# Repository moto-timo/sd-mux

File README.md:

# sd-mux

sd-mux stands for Secure Digital Multiplexer.

This is SD card switcher (multiplexer) designed to help automatic testing.

This project is sd-mux controller - binary for controlling sd-mux device.

Requirements:
  1. libftdi1 1.4 - development library
  2. popt - development library
  3. cmake - binary tool

Build:
 - enter into project directory
 - create 'build' directory
 - enter into "build" directory
 - run 'cmake ..'
 - run 'make'

Install:
 - enter into 'build' directory
 - run 'sudo make install' to install binary into '/usr/local/bin' (the default one) directory

Note:
If you want to install files into different directory then add argument to cmake command:
 cmake -DCMAKE_INSTALL_PREFIX=/usr ..
Then again run:
 make
 make install

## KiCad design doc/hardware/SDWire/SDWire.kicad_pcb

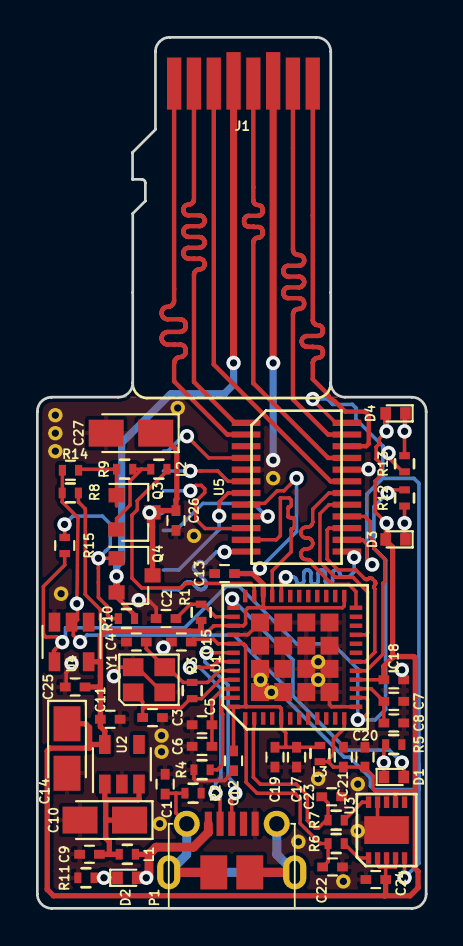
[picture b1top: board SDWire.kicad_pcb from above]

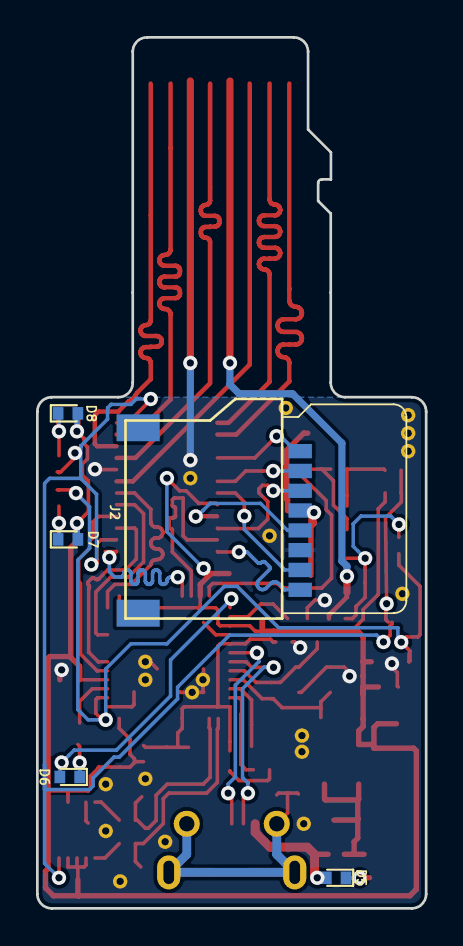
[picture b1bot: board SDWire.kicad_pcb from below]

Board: 2 copper layers, 21.6 x 48.4 mm, 63 parts (5 on the bottom side), 49 nets.

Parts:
C1, C2, C6, C8, C9, C11, C12, C13, C15, C17, C18, C20, C24, C25, C26: 100nF/16V; C_0402
C3, C4: 33p/50V; C_0402
C5, C7, C19, C21: 1uF/16V; C_0402
C10, C14, C27: 10uF/10V; CP_Tantalum_Case-A_EIA-3216-18_Reflow
C22, C23: 47pF; C_0402
D1, D6: OSB50402C1E; LED_0402
D2, D5: RED; LED_0402
D3, D7: BLUE; LED_0402
D4, D8: GREEN; LED_0402
J1: usd-plug; usd
J2: uSD Socket; usd-attend
L1, L2, L3: BLM15PD121SN1D; R_0402
P1: USB_OTG_MICRO_USB; micro_sub_molex
Q3, Q4: MMBT4403LT1; SOT-23
R1, R2, R9, R10: 10K; R_0402
R3: 1M; R_0402
R4: 12k 1%; R_0402
R5: 330R; R_0402
R6, R7: 27R; R_0402
R8: DNP; R_0402
R11, R12, R13, R14, R15: 1K; R_0402
U1: USB2640-HZH-02; QFN-48-1EP_7x7mm_Pitch0.5mm
U2: SPX3819M5; SOT-23-5
U3: FT200XD; DFN-10-1EP_3x3mm_Pitch0.5mm
U4: MC74HC1G04DTT1G; SOT-23-5
U5: TS3A27518EPWR; TSSOP-24
Y1: 24MHz; Crystal_SMD_2520-4pin_2.5x2.0mm

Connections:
+3V3: C11.1, C13.1, C14.1, C18.1, C20.1, C21.1, C24.1, C25.1, D3.2, D4.2, D7.2, D8.2, L3.1, R1.1, R8.2, U1.12, U1.16, U1.25, U1.34, U1.39, U2.5, U3.2, U3.3, U3.4, U3.7, U4.5, U5.8
/CLK_DUT: J1.5, U5.21
/CLK_TS: U1.21, U5.17
/CMD_DUT: J1.3, U5.19
/CMD_TS: U1.24, U5.18
/DAT0_DUT: J1.7, U5.23
/DAT0_TS: U1.18, U5.15
/DAT1_DUT: J1.8, U5.22
/DAT1_TS: U1.17, U5.16
/DAT2_DUT: J1.1, U5.2
/DAT2_TS: U1.33, U5.11
/DAT3_DUT: J1.2, U5.1
/DAT3_TS: U1.32, U5.13
/SOCKET_SEL: R8.1, R13.2, R14.2, U3.5, U4.2, U5.14, U5.24
/USB_B+: C23.1, R7.2, U1.2
/USB_B-: C22.1, R6.2, U1.1
/USB_UP+: P1.3, U1.42
/USB_UP-: P1.2, U1.43
/USD_VDD: C26.1, C27.1, J2.4, Q3.3, Q4.3
/VDD: D2.2, D5.2, L1.2, P1.1
/VDD_DUT: J1.4, Q4.2, R10.2
/VDD_TS: L2.1, Q3.2, R9.2
/~CD_TS: R12.2, R15.2, U1.14, U4.4
/~RESET: C2.1, R1.2, U1.38
GND: C1.2, C2.2, C3.2, C4.2, C5.2, C6.2, C7.2, C8.2, C9.2, C10.2, C11.2, C12.2, C13.2, C14.2, C15.2, C17.2, C18.2, C19.2, C20.2, C21.2, C22.2, C23.2, C24.2, C25.2, C26.2, C27.2, J1.6, J2.6, P1.5, R2.2, R4.2, R5.2, R11.2, U1.13, U1.40, U1.49, U2.2, U3.9, U3.11, U4.3, U5.5, U5.20, Y1.2, Y1.4
unnamed: C1.1, P1.6, R2.1
unnamed: C3.1, R3.2, U1.45, Y1.1
unnamed: C4.1, R3.1, U1.44, Y1.3
unnamed: C5.1, C6.1, U1.46
unnamed: C7.1, C8.1, U1.15
unnamed: C9.1, C10.1, L1.1, U2.1, U2.3
unnamed: C12.1, C15.1, C17.1, C19.1, L3.2, U1.5, U1.41, U1.48
unnamed: D1.1, D6.1, R5.1
unnamed: D1.2, D6.2, U1.37
unnamed: D2.1, D5.1, R11.1
unnamed: D3.1, D7.1, R12.1
unnamed: D4.1, D8.1, R13.1
unnamed: J2.1, U5.4
unnamed: J2.2, U5.6
unnamed: J2.3, U5.10
unnamed: J2.5, U5.9
unnamed: J2.7, U5.7
unnamed: J2.8, U5.12
unnamed: L2.2, U1.35
unnamed: Q3.1, R9.1, R14.1
unnamed: Q4.1, R10.1, R15.1
unnamed: R4.1, U1.47
unnamed: R6.1, U3.1
unnamed: R7.1, U3.10

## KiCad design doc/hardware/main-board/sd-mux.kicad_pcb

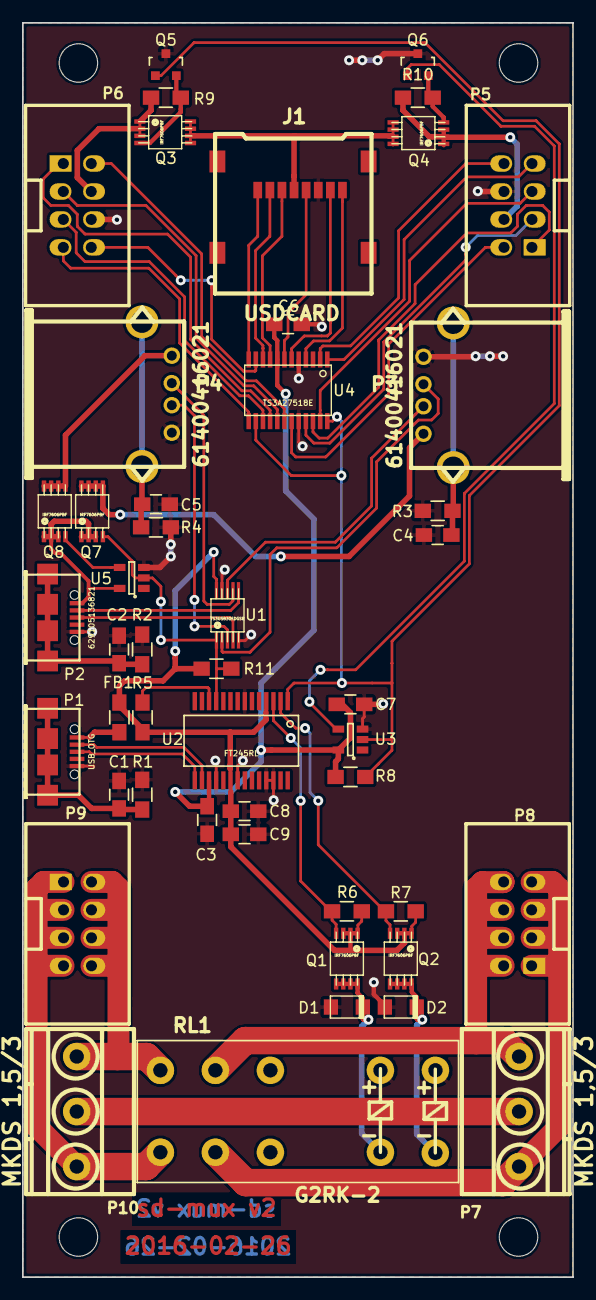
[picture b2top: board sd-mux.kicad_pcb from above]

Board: 2 copper layers, 50.0 x 114.0 mm, 48 parts (0 on the bottom side), 56 nets.

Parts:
C1, C2, C4, C5: 27p; C_0805_HandSoldering
C3, C6, C7, C8: 100n; C_0805_HandSoldering
C9: 4.7u; C_0805_HandSoldering
D1, D2: ES1AL; do219ab
FB1: MI0805K400R-10; R_0805_HandSoldering
J1: USDCARD; microsd_socket
P1: USB_OTG; conn_usb_B_micro
P2: 629105136821; conn_usb_B_micro
P3, P4: 61400416021; conn_usb_A
P5, P6: IDC_02X04; PSB_IDC_4x2
P7, P10: MKDS 1,5/3; cons_1,5x3
P8, P9: CONN_02X02; PSB_IDC__4x2
Q1, Q2, Q3, Q4, Q7, Q8: IRF7606PBF; msoic-8
Q5, Q6: 2N7002; SOT-23
R1, R2, R3, R4: 4.7K; R_0805_HandSoldering
R5, R6, R7, R8, R9, R10, R11: 10K; R_0805_HandSoldering
RL1: G2RK-2
U1: TS3USB30EDGSR; msoic-10
U2: FT245RL; ssop-28
U3, U5: 74AHC1G14; SOT-23-5
U4: TS3A27518E; tssop-24

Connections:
+3V3: C3.1, C6.1, C7.1, R8.1, U2.17, U3.5, U4.8
/CLK_DUT: P5.5, U4.23
/CLK_TS: P6.5, U4.15
/CMD_DUT: P5.3, U4.21
/CMD_TS: P6.3, U4.17
/DAT0_DUT: P5.7, U4.1
/DAT0_TS: P6.7, U4.13
/DAT1_DUT: P5.8, U4.2
/DAT1_TS: P6.8, U4.11
/DAT2_DUT: P5.1, U4.22
/DAT2_TS: P6.1, U4.16
/DAT3_DUT: P5.2, U4.19
/DAT3_TS: P6.2, U4.18
/POWER_SW_OFF: Q1.4, R6.2, U2.3
/POWER_SW_ON: Q2.4, R7.2, U2.2
/SOCKET_SEL: Q5.1, R8.2, U2.1, U3.2, U4.14, U4.24
/USB_SEL: Q7.4, R11.2, U1.1, U2.11, U5.2
/USD_VDD: J1.4, Q3.5, Q3.6, Q3.7, Q3.8, Q4.5, Q4.6, Q4.7, Q4.8
/VDD_DUT: P5.4, Q4.1, Q4.2, Q4.3, R10.1
/VDD_TS: P6.4, Q3.1, Q3.2, Q3.3, R9.1
GND: C1.2, C2.2, C3.2, C4.2, C5.2, C6.2, C7.2, C8.2, C9.2, D1.2, D2.2, J1.6, P1.5, P2.5, P3.4, P4.4, P5.6, P6.6, Q5.3, Q6.3, R1.2, R2.2, R3.2, R4.2, RL1.9, RL1.10, U1.5, U1.9, U2.7, U2.18, U2.21, U2.25, U2.26, U3.3, U4.5, U4.20, U5.3
unnamed: C1.1, P1.6, R1.1
unnamed: C2.1, P2.6, R2.1
unnamed: C4.1, P3.5, R3.1
unnamed: C5.1, P4.5, R4.1
unnamed: D1.1, Q1.5, Q1.6, Q1.7, Q1.8, RL1.2
unnamed: D2.1, Q2.5, Q2.6, Q2.7, Q2.8, RL1.1
unnamed: FB1.2, P1.1
unnamed: J1.1, U4.12
unnamed: J1.2, U4.10
unnamed: J1.3, U4.9
unnamed: J1.5, U4.7
unnamed: J1.7, U4.6
unnamed: J1.8, U4.4
unnamed: P1.2, U2.16
unnamed: P1.3, U2.15
unnamed: P2.1, Q7.1, Q7.2, Q7.3, Q8.1, Q8.2, Q8.3, U5.5
unnamed: P2.2, U1.6
unnamed: P2.3, U1.4
unnamed: P3.1, Q7.5, Q7.6, Q7.7, Q7.8
unnamed: P3.2, U1.8
unnamed: P3.3, U1.2
unnamed: P4.1, Q8.5, Q8.6, Q8.7, Q8.8
unnamed: P4.2, U1.7
unnamed: P4.3, U1.3
unnamed: P7.1, P8.1, P8.3, RL1.4
unnamed: P7.3, P8.2, P8.4, RL1.7
unnamed: P9.2, P9.4, P10.1, RL1.6
unnamed: P7.2, P10.2
unnamed: P9.1, P9.3, P10.3, RL1.5
unnamed: Q3.4, Q5.2, R9.2
unnamed: Q4.4, Q6.2, R10.2
unnamed: Q6.1, U3.4
unnamed: Q8.4, U5.4
unnamed: R5.2, U2.12
VDD: C8.1, C9.1, FB1.1, Q1.1, Q1.2, Q1.3, Q2.1, Q2.2, Q2.3, R5.1, R6.1, R7.1, R11.1, U1.10, U2.4, U2.20

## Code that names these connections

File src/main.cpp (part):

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#define SAMSUNG_VENDOR 0x04e8

// SDMUX specific definitions
#define SOCKET_SEL      (0x01 << 0x00)
#define USB_SEL         (0x01 << 0x03)
#define POWER_SW_OFF    (0x01 << 0x02)
#define POWER_SW_ON     (0x01 << 0x04)
#define DYPER1          (0x01 << 0x05)
#define DYPER2          (0x01 << 0x06)

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
int powerOff(struct ftdi_context *ftdi, unsigned char *pins) {
    // Turn on the coil
    *pins |= POWER_SW_ON;
    *pins &= ~(POWER_SW_OFF);
    if (writePins(ftdi, *pins) != EXIT_SUCCESS)
        return EXIT_FAILURE;

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    usleep(DELAY_100MS);

    // Turn off the coil
    *pins |= POWER_SW_OFF;
    if (writePins(ftdi, *pins) != EXIT_SUCCESS)
        return EXIT_FAILURE;

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
int powerOn(struct ftdi_context *ftdi, unsigned char *pins) {
    // Turn on the coil
    *pins |= POWER_SW_OFF;
    *pins &= ~(POWER_SW_ON);
    if (writePins(ftdi, *pins) != EXIT_SUCCESS)
        return EXIT_FAILURE;

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    usleep(DELAY_100MS);

    // Turn off the coil
    *pins |= POWER_SW_ON;
    if (writePins(ftdi, *pins) != EXIT_SUCCESS)
        return EXIT_FAILURE;

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
    // Currently only old SD-MUX is the other device so do the job in its style.
    if (target == T_DUT) {
        pins &= ~(USB_SEL);
        pins &= ~(SOCKET_SEL);
        if (powerOn(ftdi, &pins) != EXIT_SUCCESS) {  // Also selects USB and SD
            ret = EXIT_FAILURE;
            goto finish_him;
        }
    } else {
        pins |= USB_SEL;
        pins |= SOCKET_SEL;
        if (powerOff(ftdi, &pins) != EXIT_SUCCESS) { // Also selects USB and SD
            ret = EXIT_FAILURE;
            goto finish_him;
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           ret = EXIT_FAILURE;
           goto finish_him;
       }
       fprintf(stdout, "SD connected to: %s\n", pins & SOCKET_SEL ? "TS" : "DUT");
       goto finish_him;
    }

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    }

    // Currently only old SD-MUX is the other device so do the job in its style.
    if (!((pins & POWER_SW_ON) && (pins & POWER_SW_OFF))) {
        fprintf(stdout, "Device not initialized!\n");
        goto finish_him;
    }

    fprintf(stdout, "USB connected to: %s\n", pins & USB_SEL ? "TS" : "DUT");
    fprintf(stdout, "SD connected to: %s\n", pins & SOCKET_SEL ? "TS" : "DUT");

finish_him:
    ftdi_usb_close(ftdi);
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
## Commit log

2016-01-21 Created project
2016-04-02 Update notes for submitted changes
    * Add license file
2016-04-02 Update notes for submitted changes
    * Add sd-mux hardware documentation
2016-04-26 Update notes for submitted changes
    * Add MicroSD card adapter hardware documentation
2016-04-28 Update notes for submitted changes
    * Add bash completion script
    * Add man page for sd-mux-ctrl
    * Add command for getting current state of device
    * Add implementation of most of the functionality
    * Add project skeleton
2016-04-30 Inherit access from scm/acls/domain_scm/uncategorized
2016-05-05 Update notes for submitted changes
    * Add project skeleton
2016-05-05 Update notes for submitted changes
    * Add implementation of most of the functionality
2016-05-05 Update notes for submitted changes
    * Add command for getting current state of device
2016-05-05 Update notes for submitted changes
    * Add man page for sd-mux-ctrl
2016-05-05 Update notes for submitted changes
    * Add bash completion script
2016-05-24 Project settings updated
2016-07-01 Add dynamic jumpers (DyPer) control
2016-11-14 Fix power supply connection of USB switch incerter
    Power supply pin of U5 was connected to 3.3V. Q8, driven from this
    inverter, couldn't be fully closed as maximum output voltage from
    the inverter was 3.3V. Now, the inverter, is connected to VCC pin
    of USB connector which gives 5V.
2016-11-16 Add fabrication files for main board v 2.1
2016-11-16 Add fabrication files for uSD card adapter v 1
2016-11-17 Fix power supply connection of USB switch inverter
    Power supply pin of U5 was connected to 3.3V. Q8, driven from this
    inverter, couldn't be fully closed as maximum output voltage from
    the inverter was 3.3V. Now, the inverter, is connected to VCC pin
    of USB connector which gives 5V.
2016-11-22 Update notes for submitted changes
    * Add dynamic jumpers (DyPer) control
2017-02-15 Add PRODUCT ID option to command line interface
    This change introduces possiblity to use FTDI devices other than FT245RL.
2017-02-15 Add PRODUCT ID option to command line interface
    This change introduces possiblity of using FTDI devices
    other than FT245RL.
2017-02-15 Add device type setting in --set-serial function
    This setting is needed to distinguish one type of FTDI chip
    from another.
2017-02-16 Introduce device type and make the code use of it
    NOTE: this patch needs extra functionality of libftdi1 library.
    The functionality is ftdi_eeprom_get_strings(). Proper patch
    includeing this change was posted on upstream mailing list
    and hopefully will be merged.
2017-02-16 Introduce device features and make use of them
    Device features are used to check whether given functionality is
    available on given board or not.
2017-02-16 Implement SDWire specific SD MUX controller
2017-06-16 Introduce device type and make the code use of it
    NOTE: this patch needs extra functionality of libftdi1 library.
    The functionality is ftdi_eeprom_get_strings(). It is available
    in libftdi1 since 1.4rc1 version.
2018-02-15 Lengthen micro SD card adapter
    The lengthening had to be done mainly because of boards housings.
    Usually, walls of the housing caused prolems with inserting adapter
    into card socket. Now the adaper is 5mm longer.
2018-03-02 Add hardware documentation of SDWire device
2018-03-02 Add fabrication files for SDWire device
2018-03-02 Add fabrication files for uSD card adapter v2
2018-03-21 Require libftd1 version 1.4 or newer
    Version 1.4 is the first to support ftdi_eeprom_get_strings() function.
2018-04-05 Fix silkscreen and fabrication layers
2018-04-24 Fix LEDs and card detect connections
2019-01-08 Add support for USB-MUX device
2019-01-24 Add udev rule
    This is early draft, sent for review so it won't be forgotten.
    issues:
    1. it takes sdwire product id, i dont have a sdmux to check its ID, a
    second rule for sdmux should be added
    2. it is just added file-> should be included in package and installed
    both via deb and rpm
2020-08-28 Make the project buildable on FreeBSD
    Get CFLAGS and LDFLAGS form pop/libftdi pkg-config. On Linux
    it's no-op but required on FreeBSD since all 3rd-party packages
    are installed to /usr/local/
2024-09-22 actions: Add release.yml
    Build with jiro4989/build-deb-action@v3
2024-09-22 README -> README.md
    Move README to markdown
2024-09-22 fix: release.yml paths
    Try debian instead of .debpkg
    Try packaging instead of .rpmpkg
2024-09-22 feat: Add release.yml
    Build with jiro4989/build-deb-action@v3
2024-09-22 refactor: README -> README.md
    Move README to markdown
2024-09-22 feat: Add .chglog configuration
    Use https://github.com/git-chglog/git-chglog
2024-09-22 chore: bump git-chglog to 0.15.4
    Bump to latest upstream release
2024-09-22 fix: untar git-chglog
    Upstream bundles in a tarball now.
    Untar and run the bundled executable
2024-09-28 chore: bump compat to 10
    Fix:
    dh: warning: Compatibility levels before 10 are deprecated (level 9 in use)
2024-09-28 chore: update debian/control
    Bump debhelper requirement to >10
    Change maintainer to self
2024-09-28 chore: update CMakeLists.txt
    * Bump version
    * Update minimum cmake version to avoid deprecation warning
2024-09-28 Update debian/changelog for v0.0.3
    Summarize the recent commits.

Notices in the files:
src/main.cpp:
Copyright (c) 2016 Samsung Electronics Co., Ltd All Rights Reserved
Licensed under the Apache License, Version 2.0 (the "License");
See the License for the specific language governing permissions and
limitations under the License
